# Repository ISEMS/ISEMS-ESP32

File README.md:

# ISEMS-ESP32

This is a port of the ISEMS solar node software for ESP32 Microcontrollers from Espressif Systems. Since the OpenWRT/Linux tool is based on LUA we have chosen the ESP32 version of NodeMCU as the firmware base.

You can use a ESP32 board/module like NodeMCU, WROOM, WROVER and connect it to the serial port of the Freifunk OpenMPPT Solar controller. Simply connect GND, 3V3 and RX (OpenMPPT) <--> TX (ESP32) Pin 17, TX (OpenMPPT) --> RX (ESP32) Pin 16.

It is desirable to use a switched mode DC/DC buck converter instead of the linear voltage regulator of the Freifunk OpenMPPT. If the ESP32 operates as WiFi client, we might get away with the 100mA rating of the linear voltage regulator, but we do waste energy. If the ESP32 is set to software AP or software AP + software AP client, the ESP32 and the ATmega8 in the Freifunk OpenMPPT will lock up, due to insufficient power supply.

A Freifunk OpenMPPT pcb with ESP32 WROOM integrated is currently in the design phase. So stay tuned!

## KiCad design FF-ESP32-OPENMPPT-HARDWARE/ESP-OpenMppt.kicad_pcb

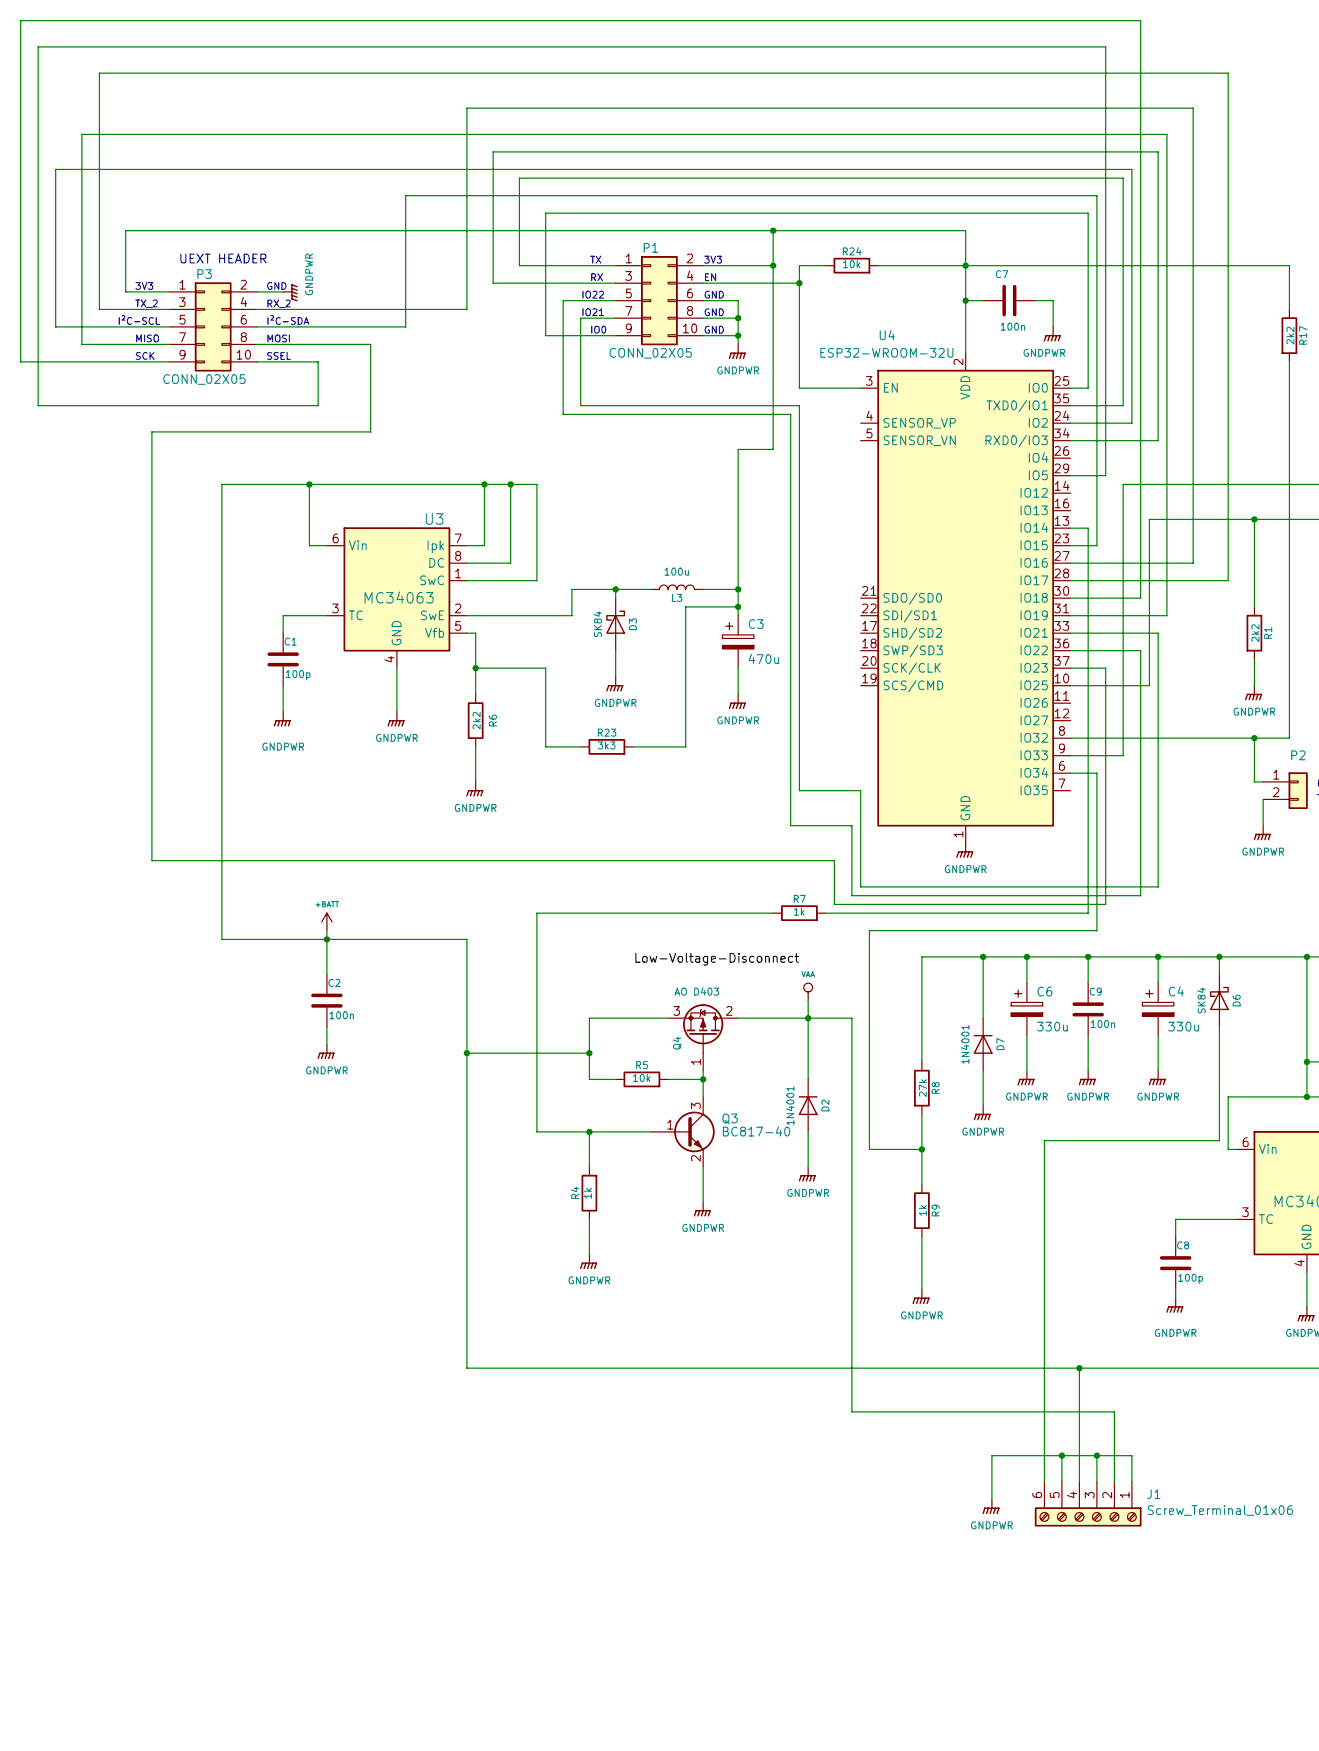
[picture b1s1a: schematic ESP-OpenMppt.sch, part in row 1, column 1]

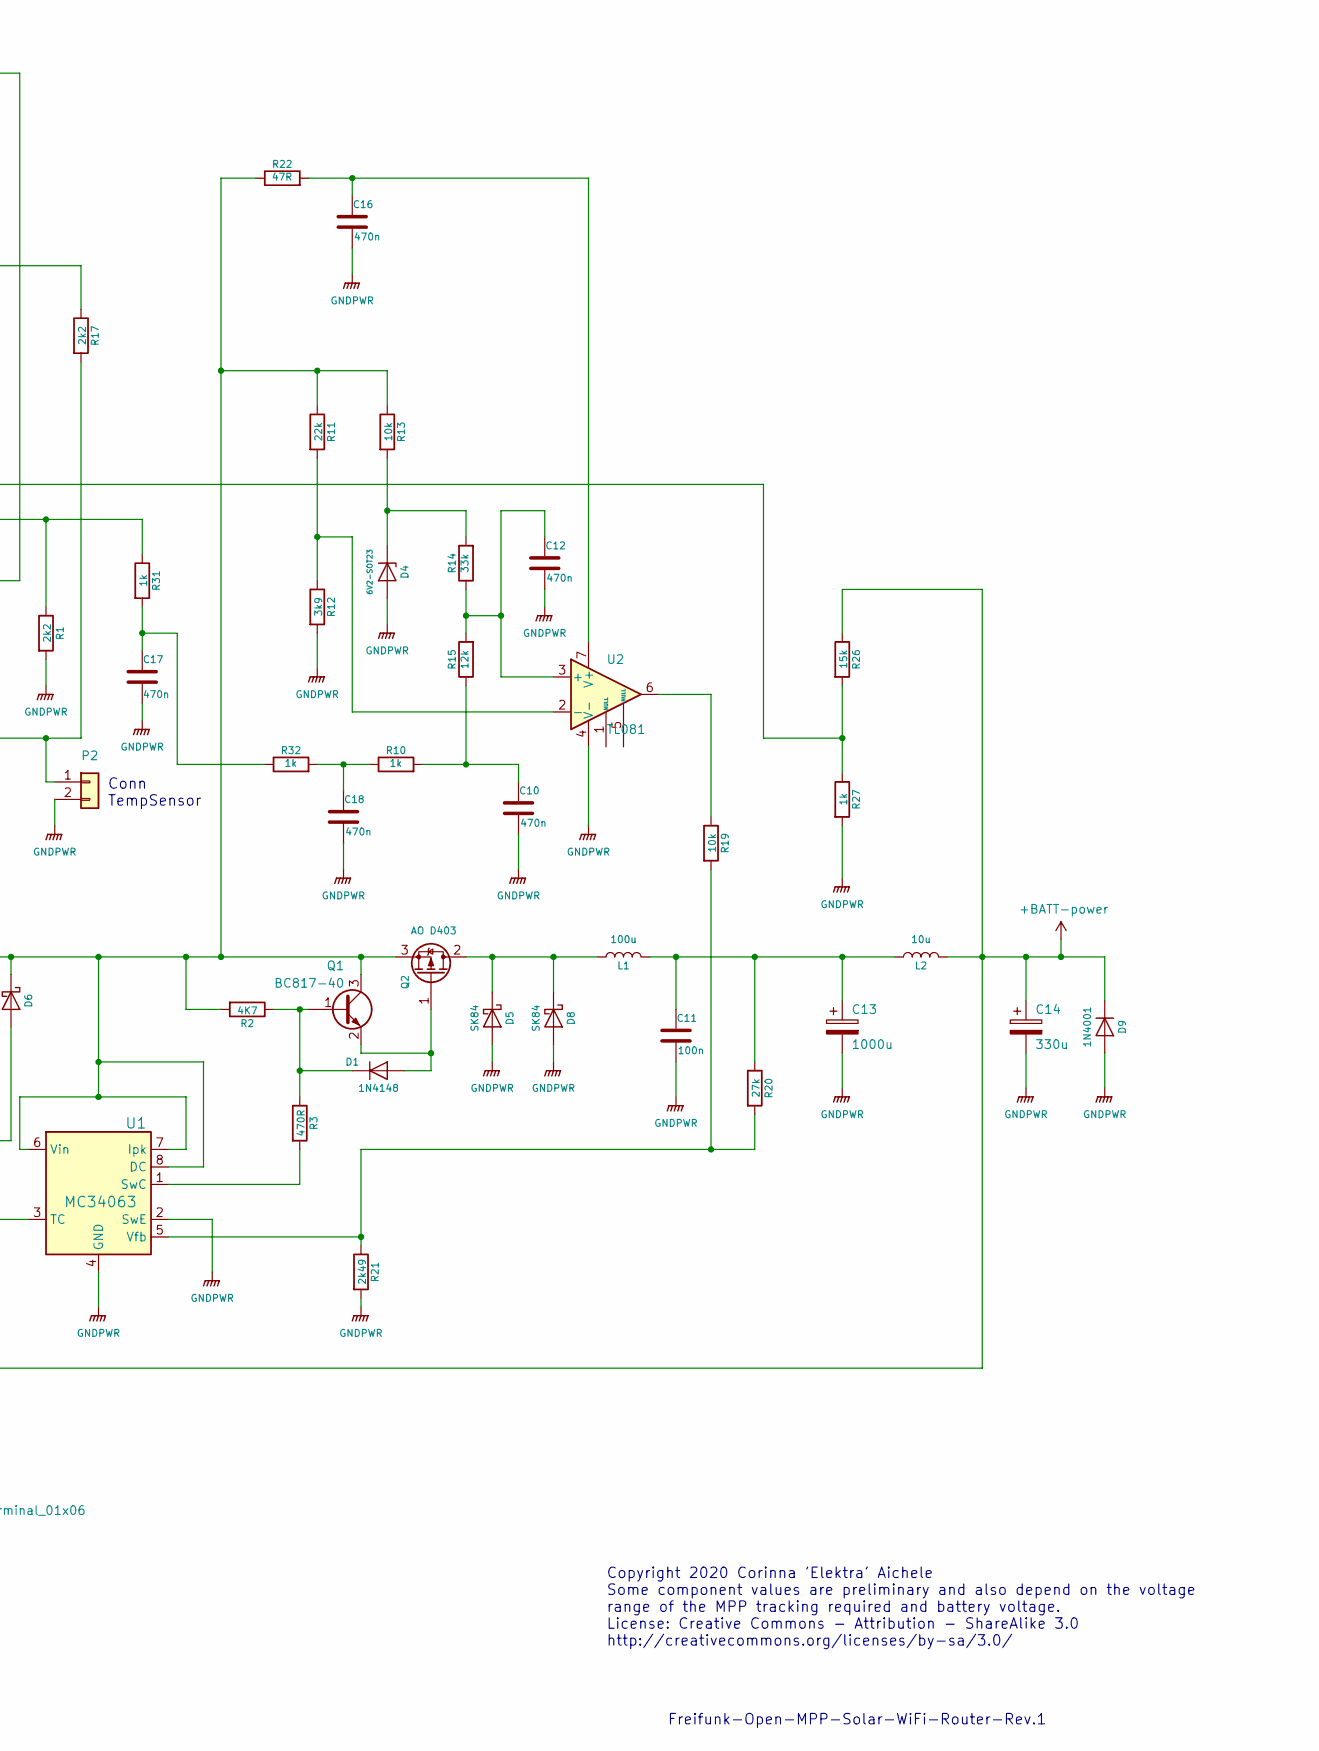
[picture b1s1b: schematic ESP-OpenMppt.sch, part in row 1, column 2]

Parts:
C1, C8: 100p; C_0805_2012Metric
C2: 100n; C_1206_3216Metric
C3: 470u; CP_Elec_8x10
C4, C6, C14: 330u; CP_Elec_10x14.3
C7, C9, C11: 100n; C_0805_2012Metric
C10, C12, C16, C17, C18: 470n; C_1206_3216Metric
C13: 1000u; CP_Elec_10x14.3
D1: 1N4148; D_1206_3216Metric
D2, D7, D9: 1N4001; D_1206_3216Metric
D3, D5, D6, D8: SK84; D_2816_7142Metric_Pad3.20x4.45mm_HandSolder
D4: 6V2-SOT23; D_1206_3216Metric
J1: Screw_Terminal_01x06; TerminalBlock_RND_205-00236_1x06_P5.08mm_Horizontal
L1: 100u; L_Toroid_Vertical_L16.8mm_W9.2mm_P7.10mm_Vishay_TJ3
L2: 10u; L_Toroid_Vertical_L10.0mm_W5.0mm_P5.08mm
L3: 100u; L_Toroid_Vertical_L10.0mm_W5.0mm_P5.08mm
P1, P3: CONN_02X05; PinHeader_2x05_P2.54mm_Vertical
P2: CONN_01X02; PinHeader_1x02_P2.54mm_Vertical
Q1, Q3: BC817-40; SOT-23
Q2, Q4: AO D403; TO-252-2Lead
R1, R6, R17: 2k2; R_0805_2012Metric
R2: 4K7; R_0805_2012Metric
R3: 470R; R_0805_2012Metric
R4, R7, R9, R10, R27, R31, R32: 1k; R_0805_2012Metric
R5, R13, R19, R24: 10k; R_0805_2012Metric
R8, R20: 27k; R_0805_2012Metric
R11: 22k; R_0805_2012Metric
R12: 3k9; R_0805_2012Metric
R14: 33k; R_0805_2012Metric
R15: 12k; R_0805_2012Metric
R21: 2k49; R_0805_2012Metric
R22: 47R; R_0805_2012Metric
R23: 3k3; R_0805_2012Metric
R26: 15k; R_0805_2012Metric
U1, U3: MC34063; SOIC-8-1EP_3.9x4.9mm_P1.27mm_EP2.29x3mm
U2: TL081; SOIC-8-1EP_3.9x4.9mm_P1.27mm_EP2.29x3mm
U4: ESP32-WROOM-32U

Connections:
+BATT: C2.1, C14.1, D9.1 (K), J1.4, L2.2, Q4.3 (S), R5.1, R26.1, U3.1 (SwC), U3.6 (Vin), U3.7 (Ipk), U3.8 (DC)
GNDPWR: C1.2, C2.2, C3.2, C4.2, C6.2, C7.2, C8.2, C9.2, C10.2, C11.2, C12.2, C13.2, C14.2, C16.2, C17.2, C18.2, D2.2 (A), D3.2 (A), D4.2 (A), D5.2 (A), D7.2 (A), D8.2 (A), D9.2 (A), J1.1, J1.3, J1.5, P1.6, P1.8, P1.10, P2.2, P3.2, Q3.2 (E), R1.2, R4.1, R6.2, R9.2, R12.2, R21.2, R27.2, U1.2 (SwE), U1.4 (GND), U2.4 (V-), U3.4 (GND), U4.1 (GND), U4.15 (GND), U4.38 (GND), U4.39 (GND); also elsewhere on the board
unnamed: C1.1, U3.3 (TC)
unnamed: C3.1, C7.1, L3.2, P1.2, P3.1, R17.1, R23.2, R24.2, U4.2 (VDD)
unnamed: C4.1, C6.1, C9.1, D6.1 (K), D7.1 (K), Q1.3 (C), Q2.3 (S), R2.2, R8.1, R11.1, R13.1, R22.1, U1.6 (Vin), U1.7 (Ipk), U1.8 (DC)
unnamed: C8.1, U1.3 (TC)
unnamed 6: C10.1, R10.2, R15.1; also elsewhere on the board
unnamed: C11.1, C13.1, L1.2, L2.1, R20.1
unnamed: C12.1, R14.1, R15.2, U2.3 (+)
unnamed: C16.1, R22.2, U2.7 (V+)
unnamed: C17.1, R31.2, R32.1
unnamed: C18.1, R10.1, R32.2
unnamed: D1.1 (K), Q1.1 (B), R2.1, R3.1
unnamed: D1.2 (A), Q1.2 (E), Q2.1 (G)
unnamed: D3.1 (K), L3.1, U3.2 (SwE)
unnamed: D4.1 (K), R13.2, R14.2
unnamed: D5.1 (K), D8.1 (K), L1.1, Q2.2 (D)
unnamed: D6.2 (A), J1.6
unnamed: P1.1, U4.35 (TXD0/IO1)
unnamed: P1.3, U4.34 (RXD0/IO3)
unnamed: P1.4, R24.1, U4.3 (EN)
unnamed: P1.5, U4.36 (IO22)
unnamed: P1.7, U4.33 (IO21)
unnamed: P1.9, U4.25 (IO0)
unnamed: P2.1, R17.2, U4.8 (IO32)
unnamed: P3.3, U4.28 (IO17)
unnamed: P3.4, U4.27 (IO16)
unnamed: P3.5, U4.24 (IO2)
unnamed: P3.6, U4.23 (IO15)
unnamed: P3.7, U4.31 (IO19)
unnamed: P3.8, U4.37 (IO23)
unnamed: P3.9, U4.30 (IO18)
unnamed: P3.10, U4.29 (IO5)
unnamed: Q3.1 (B), R4.2, R7.1
unnamed: Q3.3 (C), Q4.1 (G), R5.2
unnamed: R1.1, R31.1, U4.10 (IO25)
unnamed: R3.2, U1.1 (SwC)
unnamed: R7.2, U4.13 (IO14)
unnamed: R8.2, R9.1, U4.6 (IO34)
unnamed: R11.2, R12.1, U2.2 (-)
unnamed: R19.1, U2.6
unnamed: R19.2, R20.2, R21.1, U1.5 (Vfb)
unnamed: R6.1, R23.1, U3.5 (Vfb)
unnamed: R26.2, R27.1, U4.9 (IO33)
VAA: D2.1 (K), J1.2, Q4.2 (D)

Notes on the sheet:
Freifunk-Open-MPP-Solar-WiFi-Router-Rev.1
Copyright 2020 Corinna 'Elektra' Aichele Some component values are preliminary and also depend on the voltage range of the MPP tracking required and battery voltage. License: Creative Commons - Attribution - ShareAlike 3.0 http://creativecommons.org/licenses/by-sa/3.0/
Conn TempSensor
GND
IO0
3V3
IO22
IO21
TX_2
RX_2
I²C-SCL
I²C-SDA
MISO
MOSI
SCK
SSEL
UEXT HEADER

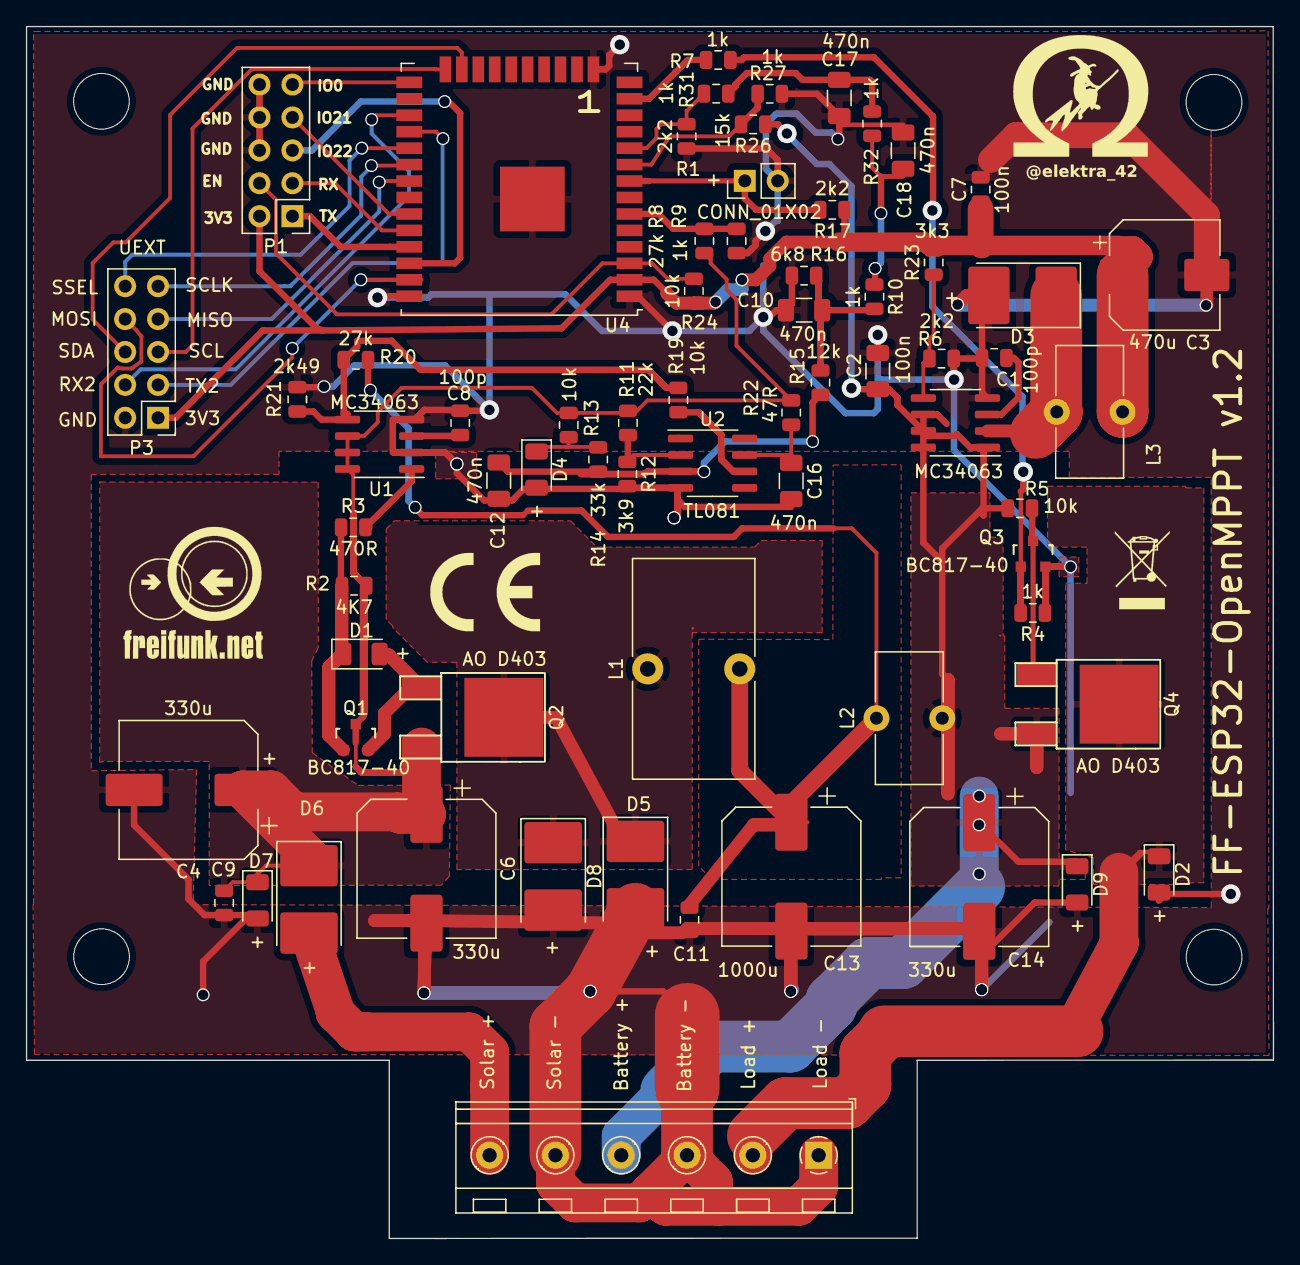
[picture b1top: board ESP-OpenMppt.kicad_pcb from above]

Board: 2 copper layers, 96.2 x 93.6 mm, 67 parts (0 on the bottom side), 45 nets.

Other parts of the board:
R16: 6k8; R_0805_2012Metric

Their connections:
GNDPWR: R16.2; also elsewhere on the board
unnamed 6: R16.1; also elsewhere on the board

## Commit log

2019-10-07 Generate Readme.md
2019-12-03 Adding LUA files. Preliminary version of ISEMS for external module.
2019-12-03 Added missing variable for watchdog.
2020-01-09 Commit changes to config.lua and adding the full set of LUA files to run the new hardware board. Fixed temp sensor detect bug and battery charge state estimate bug.
2020-01-09 Removed some debugging print outputs.
2020-01-15 Add changelog
2020-01-15 Add dry-dock environment
2020-01-15 Add MQTT- and HTTP-based telemetry with JSON encoding.
    Instead of sending CSV data only, this optionally
    submits self-describing metrics payloads encoded
    in JSON to an MQTT broker or a HTTP endpoint.
    This makes it easy for many kinds of downstream
    systems to ingest and process the telemetry data
    coming out of this appliance.
2020-01-16 Fixed a bug in http post routine.
2020-01-19 Improve telemetry configuration
2020-01-19 Fix MQTT telemetry
2020-01-19 Exclude some fields from telemetry payload
2020-01-21 Updated and improved MQTT telemetry file and config section.
2020-01-21 Mixed up endpoint suffixes of MQTT vs. HTTP. This fixes that glitch.
2020-01-23 Fixed HTTP telemetry upload.
2020-02-10 Adding Telnet LUA shell, minimal Unix-like telnet shell, remote load on/off switch, temperature controlled battery charge voltage.
2020-02-11 Minor bugfix.
2020-02-13 Added support for sha256'ed one-time web key. Added calibration and Lua code uploading documentation.
2020-02-13 Added SDK folder, nodemcu sdk configuration and firmware upload howto.
2020-02-13 Fixed incorrect value for low-voltage disconnect.
2020-02-13 Fix whitespace within "is.lua"
2020-02-13 Reformat HTTP server code
    In order to improve readability and to aid for better
    maintenance, we drilled through the HTTP server code
    and reformatted it slightly.
2020-02-13 Refactor HTTP server
    This gives the dispatcher some love which invokes actions over HTTP.
2020-02-13 Use HTTP POST requests for invoking action commands
    Invoking actions using HTTP GET is inherently dangerous,
    we should use HTTP POST requests exclusively for that.
    See also https://github.com/ISEMS/ISEMS-ESP32/issues/5.
2020-02-13 Adjust HTML help page
    This reflects the HTTP POST requirement for invoking action commands
    within the respective documentation available via /help.
    It also adds command line examples which can be conveniently used
    for invoking such actions and for uploading the "config.lua" file.
2020-02-16 Fix typo.
2020-02-16 Revert "Fix typo." accidently committed by root.
    This reverts commit 9b7b455a23801e5b6969f8678b2fb41f893aeec1.
2020-02-16 Fix crash due to missing random string in http code.
2020-02-18 Disabled setting the wifi station name, as this seems to break wifi.
2020-02-19 Adding precompiled firmware binaries and flashing instructions with esptool.
2020-02-21 Added draft Howto for beginners.
2020-02-21 Disabled HTTP POST method check. Added Licenses and list of contributors as far as feasible.
2020-02-21 Added FTP configuration upload section to the beginnners HOWTO.
2020-02-23 Improved accuracy of battery charge level. Updated the HTTP help page.
2020-03-06 Adding shell utility for remote control.
2020-03-22 Add reply if ftp is already running.
2020-03-22 Add ftpserver module.
2020-04-13 Improved accuracy of battery charge estimate.
2020-05-05 Adding license notes for hardware design files.
2020-05-05 Adding hardware design files.
2020-05-05 Improvements to is.lua and mp2.lua. Added modification hints for owners of prototype devices.
2020-05-05 Fixed text formatting of NOTE-ON-BOARD-REVISIONS.md
2020-05-05 Fixed typo.
